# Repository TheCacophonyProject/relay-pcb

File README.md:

# relay-pcb

A relay board that lets a thermal camera switch another device on and off. The relay contacts are
isolated from the camera.

## Wiring

### Power and control (one of these)

- **Camera plug (J1):** connect the M16 cable from the camera's output plug. The camera powers the
  board and switches the relay.
- **Screw terminal (J3):**

  | Terminal | Connect to |
  | --- | --- |
  | 12V | 12V supply (+) |
  | GND | supply ground (-) |
  | SIG | control signal: 3.3V to 12V = relay on, 0V or unconnected = relay off |

### Switched device (J2)

Wire the device you want to switch to the J2 screw terminal:

| Terminal | Use |
| --- | --- |
| COM | common, always used |
| NO | normally open: connected to COM only when the relay is on |
| NC | normally closed: connected to COM only when the relay is off |

For most uses, wire the device's supply through COM and NO, so the device only gets power while the
relay is on.

The red LED lights while the relay is on.

## License

CERN Open Hardware Licence Version 2 - Weakly Reciprocal (see [LICENSE](LICENSE)).

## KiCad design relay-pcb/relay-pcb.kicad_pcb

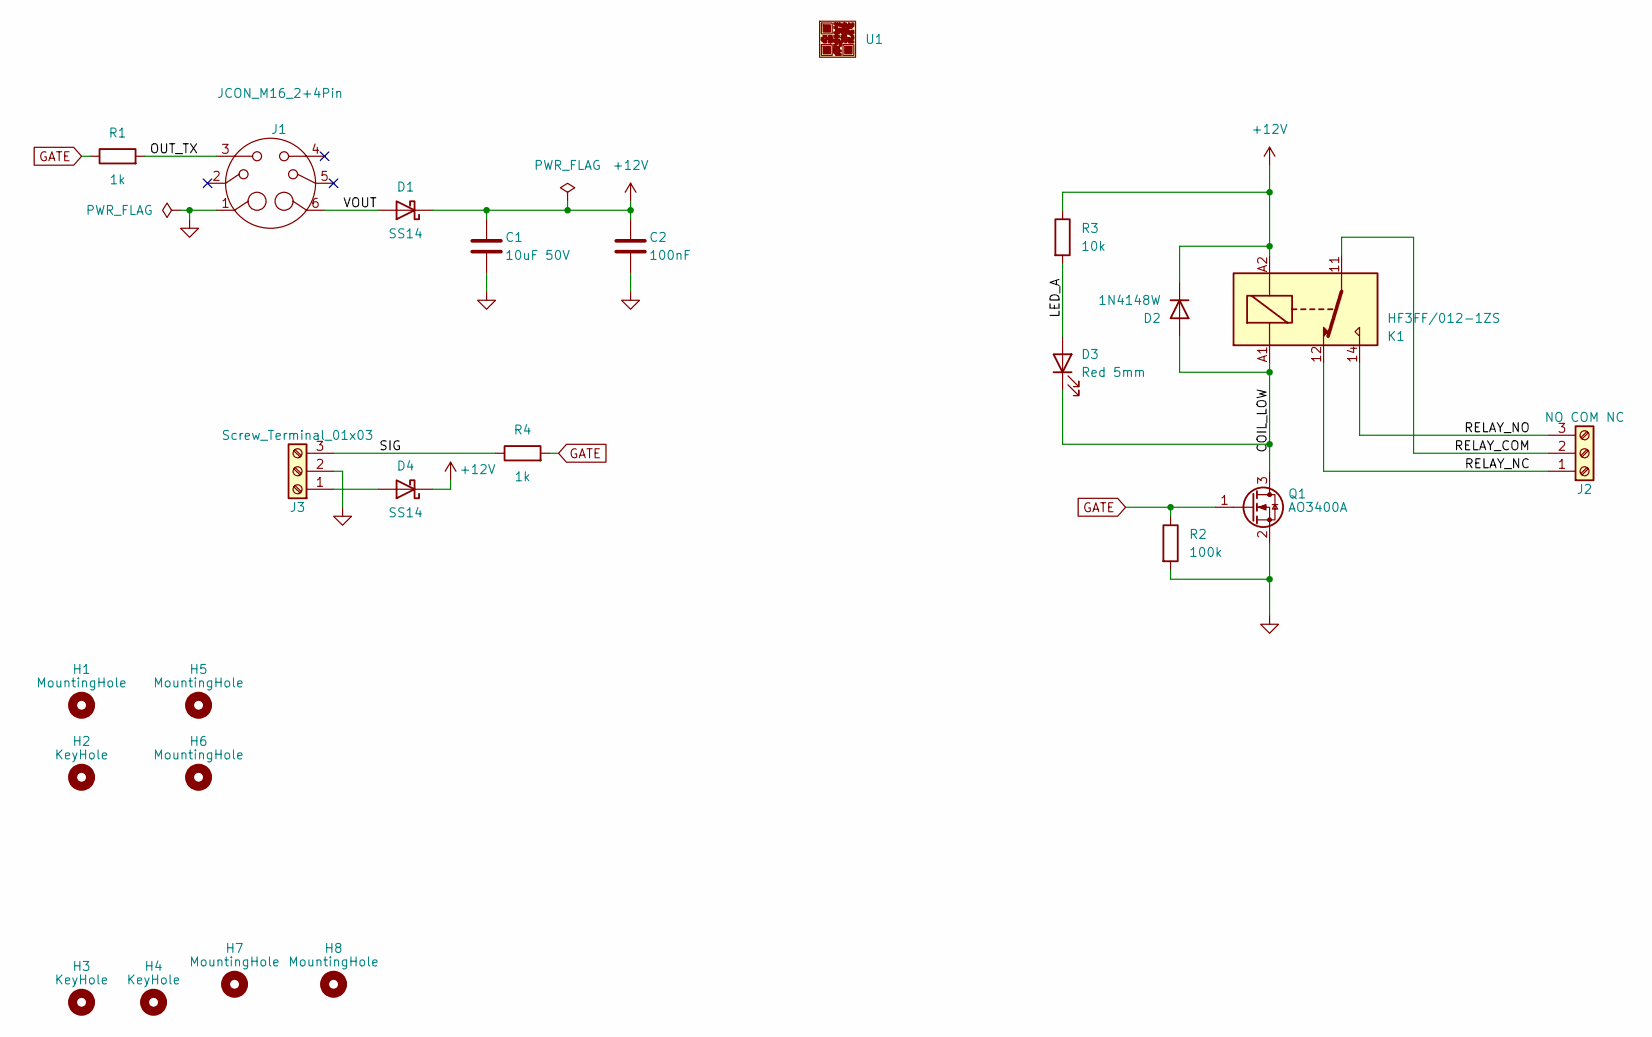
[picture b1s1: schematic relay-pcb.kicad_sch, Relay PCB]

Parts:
C1: 10uF 50V; C_1206_3216Metric_Pad1.33x1.80mm_HandSolder; LCSC Part C13585
C2: 100nF; C_0805_2012Metric_Pad1.18x1.45mm_HandSolder; LCSC Part C49678
D1, D4: SS14; D_SMA_Handsoldering; LCSC Part C2480
D2: 1N4148W; D_SOD-123; LCSC Part C81598
D3: Red 5mm; LED_D5.0mm; LCSC Part C473833
H1, H5, H6: MountingHole; MountingHole_3.2mm_M3
H2: KeyHole; 3.0mm_key_hole
H3, H4: KeyHole; KeyHole_1.8mm
H7, H8: MountingHole; MountingHole_1.8mm_M1.6
J1: JCON_M16_2+4Pin; jcon-2+4pin-m16
J2: NO COM NC; TerminalBlock_Phoenix_MKDS-1,5-3-5.08_1x03_P5.08mm_Horizont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; LCSC Part C474953
J3: Screw_Terminal_01x03; TerminalBlock_Phoenix_MKDS-1,5-3-5.08_1x03_P5.08mm_Horizont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; LCSC Part C474953
K1: HF3FF/012-1ZS; Relay_SPDT_Hongfa_JQC-3FF_0XX-1Z; LCSC Part C399561
Q1: AO3400A; SOT-23_Handsoldering; LCSC Part C20917
R1, R4: 1k; R_0805_2012Metric_Pad1.20x1.40mm_HandSolder; LCSC Part C17513
R2: 100k; R_0805_2012Metric_Pad1.20x1.40mm_HandSolder; LCSC Part C149504
R3: 10k; R_0805_2012Metric_Pad1.20x1.40mm_HandSolder; LCSC Part C17414
U1: JLCPCB_QR_8mm

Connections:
+12V: C1.1, C2.1, D1.1 (K), D2.1 (K), D4.1 (K), K1.A2, R3.1
/COIL_LOW: D2.2 (A), D3.1 (K), K1.A1, Q1.3 (D)
/LED_A: D3.2 (A), R3.2
/OUT_TX: J1.3, R1.2
/RELAY_COM: J2.2, K1.11
/RELAY_NC: J2.1, K1.12
/RELAY_NO: J2.3, K1.14
/SIG: J3.3, R4.1
/VOUT: D1.2 (A), J1.6
GATE: Q1.1 (G), R1.1, R2.1, R4.2
GND: C1.2, C2.2, J1.1, J3.2, Q1.2 (S), R2.2
unnamed: D4.2 (A), J3.1

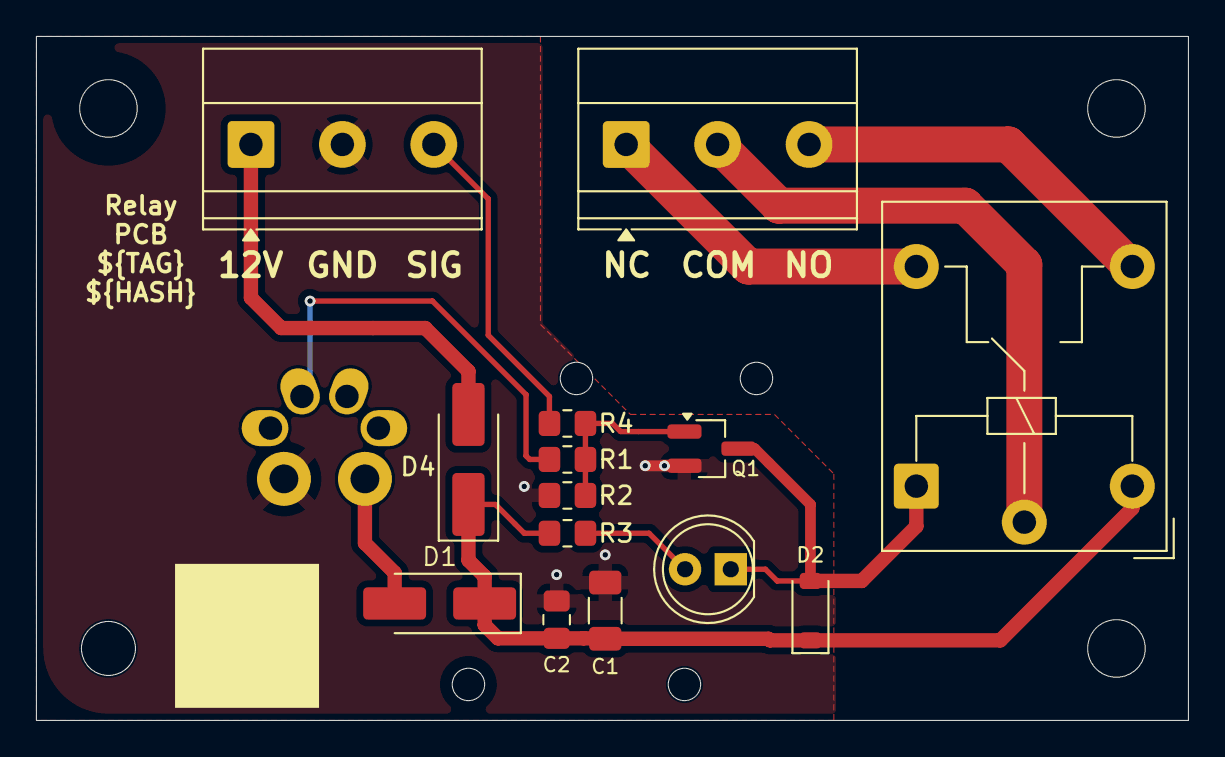
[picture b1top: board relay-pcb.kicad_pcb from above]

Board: 2 copper layers, 64.0 x 38.0 mm, 24 parts (0 on the bottom side), 12 nets.
